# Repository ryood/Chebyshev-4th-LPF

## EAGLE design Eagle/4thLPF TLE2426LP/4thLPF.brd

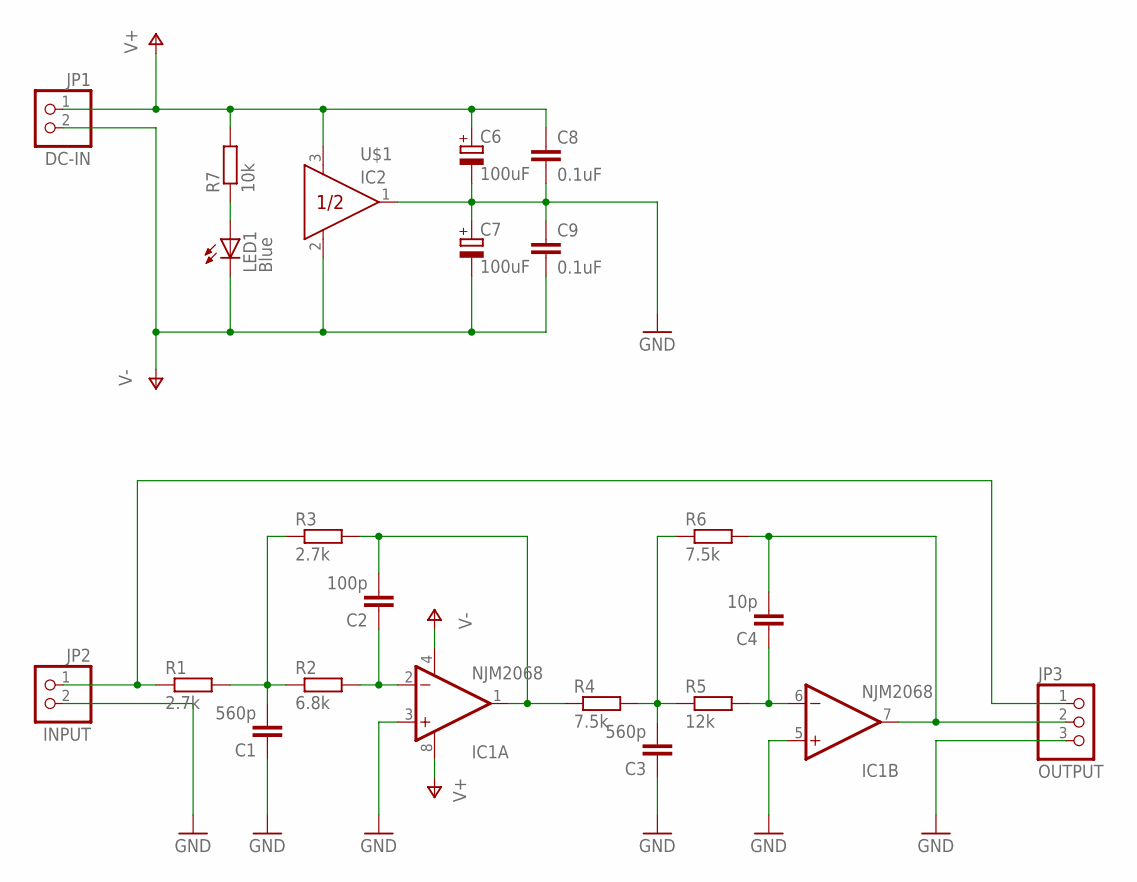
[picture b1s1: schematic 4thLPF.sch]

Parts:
C1, C3: 560p; C050-035X075
C2: 100p; C050-035X075
C4: 10p; C050-024X044
C6, C7: 100uF; E2,5-6
C8: 0.1uF; C050-024X044
C9: 0.1uF; C025-024X044
IC1: NJM2068; DIL08
JP1: DC-IN; 1X02
JP2: INPUT; 1X02
JP3: OUTPUT; 1X03
LED1: Blue; LED3MM
R1, R3: 2.7k; 0207/7
R2: 6.8k; 0207/7
R4, R6: 7.5k; 0207/7
R5: 12k; 0207/7
R7: 10k; 0207/7
U$1: IC2; TO226AA

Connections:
GND: C1.1, C3.1, C6.-, C7.+, C8.2, C9.1, IC1.3 (+IN), IC1.5 (+IN), JP2.2, JP3.3, U$1.1 (OUT)
unnamed: C1.2, R1.2, R2.1, R3.1
unnamed: C2.1, IC1.2 (-IN), R2.2
unnamed: C4.1, IC1.6 (-IN), R5.2
unnamed: C2.2, IC1.1 (OUT), R3.2, R4.1
unnamed: JP2.1, JP3.1, R1.1
unnamed: C3.2, R4.2, R5.1, R6.1
unnamed: C4.2, IC1.7 (OUT), JP3.2, R6.2
unnamed: LED1.A, R7.1
V+: C6.+, C8.1, IC1.8 (V+), JP1.1, R7.2, U$1.3 (IN)
V-: C7.-, C9.2, IC1.4 (V-), JP1.2, LED1.K (C), U$1.2 (COM)

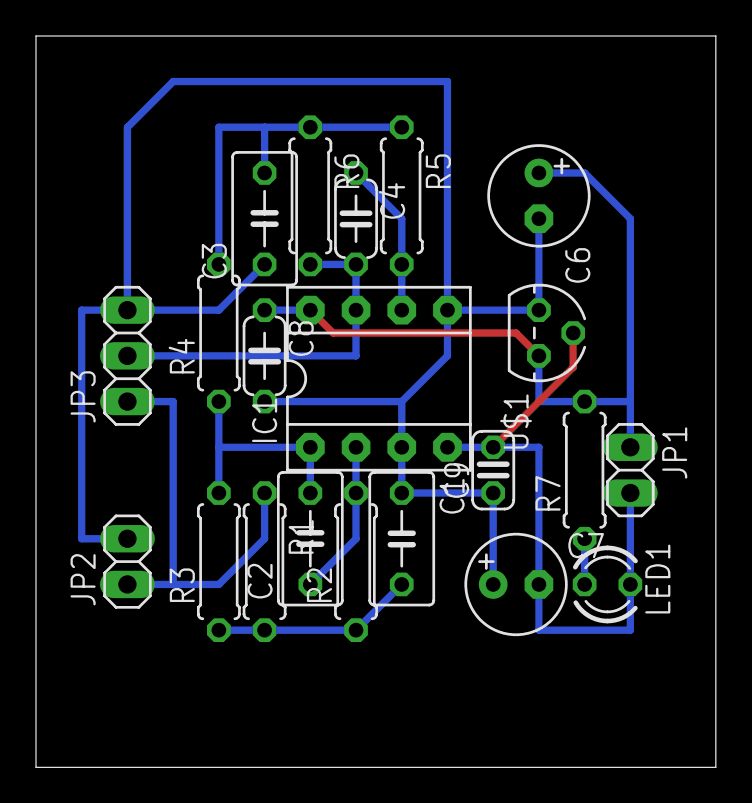
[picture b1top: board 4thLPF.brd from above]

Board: 2 copper layers, 37.8 x 40.6 mm, 21 parts (0 on the bottom side), 11 nets.

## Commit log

2016-03-10 Add: Eagle Files
2016-03-12 Update: Eagle Files
2016-03-12 基板図作成
2016-03-12 ADD: TLE2426LP Eagle Files
2016-03-12 ADD: ケース内配線
